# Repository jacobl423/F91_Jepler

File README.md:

# F91_Jepler

## Project Overview

The **F91_Jepler** is a complete redesign and evolution of the classic Casio F91W watch, inspired by the original [F91 Kepler](https://github.com/drpykachu/F91_Kepler) project. This project completely replaces the original internals of the watch, keeping only the original resin case and buttons, while adding an OLED display, a powerful Bluetooth-capable MCU, and a rechargeable battery system.

The redesign is in progress. Emulation, tooling and companion software are far along; the nRF52840 board itself is not fabricated, and fit and charging arrangements are not yet verified.

## Progress at a Glance

| Area | Status |
|---|---|
| **Hardware** | Original Kepler DipTrace PCBs converted to editable KiCad 10 projects; redesign draft board carried in the workbench app; BOMs and clock requirements documented. Nothing fabricated yet. |
| **Firmware** | Zephyr RTOS app boots under MCUboot in Renode: RTC-backed ticking clock, SSD1306 framebuffer over I2C, and the custom Notification and Clock GATT services ported to the Zephyr BLE stack. |
| **Emulation** | One-command firmware build with SHA-256 manifest, signed-image boot verification, browser watch viewer with real emulated framebuffer and GPIO buttons, headless boot check. |
| **Jepler Dev (macOS)** | Full Swift workbench: Renode session harness, UART terminal, watch face, firmware build/verify, automated test runner, UART test-bridge injectors, and a live KiCad suite (auto-reload viewer, 3D raytrace, DRC, Gerber export, diff). |
| **Companion app** | React + Capacitor mobile app (Android/iOS) with BLE scan/connect, GATT clock sync, mock driver and LCD watch face; **327/327 tests passing** (`npm test` in `Software/companion_app`). |

## Hardware Upgrades & Architecture

The original Kepler boards were authored in DipTrace; those files are retained unchanged in [`Hardware/PCB/`](Hardware/PCB) and have been converted into editable KiCad projects in [`Hardware/KiCad/`](Hardware/KiCad) (main board, display connector, debugger connector).

The nRF52840 redesign draft (A0) previously lived under `Hardware/KiCad/drafts/f91_jepler/`; that standalone copy was removed when the original boards were converted, and the same draft PCB now ships inside the workbench app at [`Software/macOS_App/F91JeplerEmulator/Resources/Embedded/f91_jepler.kicad_pcb`](Software/macOS_App/F91JeplerEmulator/Resources/Embedded/f91_jepler.kicad_pcb), where the Jepler Dev PCB tools open it by default. It remains an **unrouted electrical-core and placement draft, not a fabrication release**.

- **MCU:** Nordic nRF52840-QIAA, 7 × 7 mm AQFN73, with 1 MB flash and 256 KB RAM.
- **Display:** BuyDisplay ER-OLED0.83-1, a 0.83″ 96 × 39 monochrome OLED driven over I2C (SSD1306-class, Zephyr CFB framebuffer). Connector and supply details remain provisional.
- **Battery:** A small protected single-cell LiPo secured to the assembly replaces the earlier rechargeable coin-cell plan. Exact cell and fit remain provisional.
- **Power:** The draft includes a 3.0 V regulator (not a charger). Onboard charging, charge/load management and the charging connector still need design work.
- **Timekeeping:** External 32.768 kHz crystal feeding the nRF52840 RTC; see [clock circuit requirements](Hardware/CLOCKING.md).
- **Sensors:** An accelerometer and external flash remain optional; neither is in the draft.

### Bracket and charging contacts

Retain the original bracket as the mechanical reference. Its continuity, spring geometry, insulation and clearance around a new battery have not been measured. The user does not currently have it available, so those aspects remain provisional. The draft does not connect the bracket to a battery or charging net. Earlier split-cage and button-charging ideas in the historical project context are not approved electrical designs.

## Software Architecture

Moving to the nRF52840 means the original Texas Instruments SimpleLink firmware is being completely replaced. The new firmware is built on:
- **Zephyr RTOS / nRF Connect SDK:** The modern standard for Nordic BLE development.
- **MCUboot + SMP Server:** MCUboot is the first-stage bootloader with RSA-2048 signed images, and the SMP server allows safe, dual-bank Over-The-Air (OTA) Device Firmware Updates (DFU) directly from a smartphone, so the watch never needs to be opened for programming once flashed.

See [`Firmware/README.md`](Firmware/README.md) for build commands, the GATT service/characteristic map, and flashing notes.

## Development Tooling

### Jepler Dev — macOS workbench (`Software/macOS_App`)

A Swift app that combines the emulator, firmware pipeline and PCB tooling in one window:

- **Renode session harness:** launches Renode with the signed app image and matching MCUboot ELF, streams the UART console, and renders the live emulated framebuffer in a watch frame (the screen is driven by an in-repo `F91SSD1306.cs` model, not a mock drawing).
- **Firmware build & verify:** builds the Zephyr app plus its matching MCUboot image, signs it, and verifies full-file SHA-256 hashes against the generated `firmware-manifest.json` before loading anything into a session.
- **Automated tests & injectors:** boot-test runner and button-sequence presets that assert on firmware-reported state over the emulator-only UART test bridge, plus Notification/Clock service test panels (service-handler payloads, not real BLE/ATT traffic).
- **KiCad suite:** live auto-reload PCB viewer, 3D raytrace render, DRC via `kicad-cli` with SHA-256-pinned input snapshots and explicit pass / fail / inconclusive confidence, Gerber export, PCB diff and comparison, component inspector, board validation and GPIO pin audit against the compiled devicetree.

Build and launch from the repo root:

```bash
./run_emulator.sh          # builds "Jepler Dev.app" if missing, then opens it
```

### Emulation without the app (`Firmware/renode`)

```bash
bash Firmware/renode/build-display.sh   # west build + sign app & MCUboot, export manifest
bash Firmware/renode/watch-ui.sh        # watch viewer at http://127.0.0.1:8085
bash Firmware/renode/boot-check.sh      # headless MCUboot + app boot verification
```

See [`Firmware/renode/README.md`](Firmware/renode/README.md) for details, key bindings, and known limitations.

### Companion app (`Software/companion_app`)

React + Capacitor app for Android/iOS: scans for the watch by name or Clock Service UUID, connects over BLE, and syncs time / timezone / time mode / DST through the GATT clock characteristics, with a simulated-watch driver and an F-91W-style LCD for development. The suite covers serialization boundaries, the connection state machine, sync fault injection and a 4-tier E2E integration suite.

```bash
cd Software/companion_app
npm test          # Vitest: 327/327 passing
npm run typecheck && npm run build
```

## Current Project Status

- **Mechanicals:** Provisional outline and battery envelope; bracket fit unverified.
- **Schematic & PCB:** Original DipTrace boards converted to editable KiCad projects under [`Hardware/KiCad`](Hardware/KiCad); the nRF52840 redesign remains an unrouted draft (bundled with the macOS app). Original DipTrace files retained.
- **Firmware:** Zephyr, MCUboot and the ported GATT services run in Renode; see [emulation instructions](Firmware/renode/README.md). Signed-image boot and a flipped-byte rejection check pass; OTA swapping/rollback has not been tested. Simulation does not validate the physical board.
- **Software:** Jepler Dev workbench builds and launches via `run_emulator.sh`; companion app tests, typecheck and production build pass.

## Collaboration and Setup
Welcome collaborators! To get started with the repository, follow these steps:

1. **Clone the repository**:
   ```bash
   git clone <repository_url>
   cd f91_jepler
   ```

2. **Set up the Python Environment**:
   This project includes some utility scripts for parsing BOMs and STL files, and the Zephyr/west build uses the same environment. It is recommended to use a virtual environment:
   ```bash
   python3 -m venv .venv
   source .venv/bin/activate
   pip install -r requirements.txt
   ```

3. **Project Structure**:
   - `Firmware/`: Zephyr firmware source and Renode emulation tooling.
   - `Hardware/`: PCB designs (DipTrace originals and KiCad conversions), schematics, and BOMs.
   - `Software/`: Companion mobile app (`companion_app`), the Jepler Dev macOS workbench (`macOS_App`), and the legacy Android shell (`app`).

4. **Contributing**:
   - Please create a new branch for any feature or bugfix (e.g., `feature/add-new-sensor` or `bugfix/fix-display-glitch`).
   - Open a pull request against the `main` branch when your changes are ready for review.

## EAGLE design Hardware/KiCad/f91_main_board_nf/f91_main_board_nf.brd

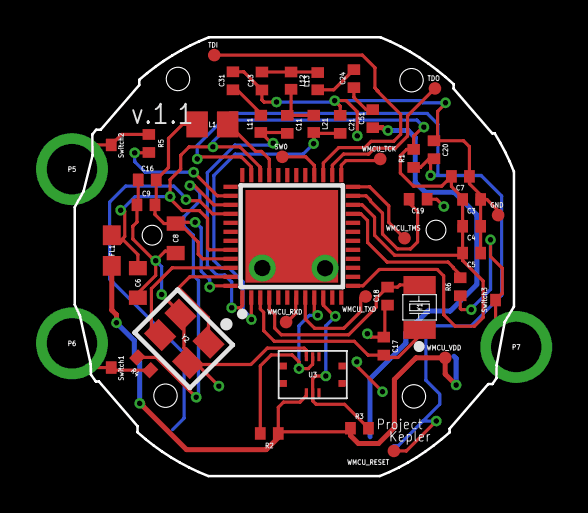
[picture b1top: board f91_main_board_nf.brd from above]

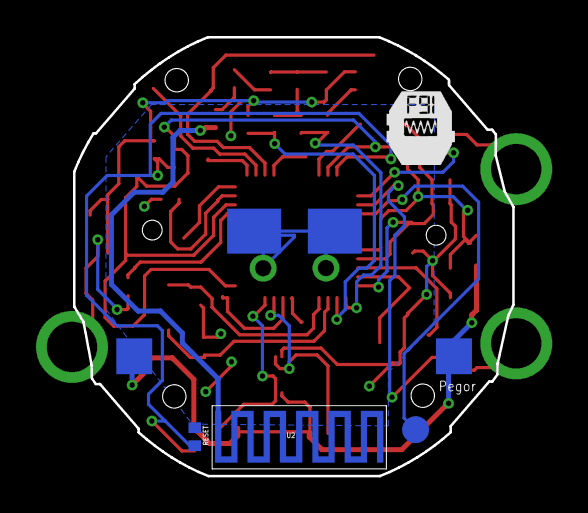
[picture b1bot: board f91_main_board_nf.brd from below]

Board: 2 copper layers, 24.4 x 24.4 mm, 59 parts (7 on the bottom side), 35 nets.

Parts:
: CC2640(long pads); RGZ0048A-VQFN-48(longer_pads)
C3, C4, C5, C7, C9, C16, C20: 100nF; CAP_0402
C6, C8: 10uF; CAP_0603
C11, C13, C21: 1pF; CAP_0402
C17, C18, C24: 12pF; CAP_0402
C19: 1uF; CAP_0402
C31: 6.8pF; CAP_0402
C51: 1.8pF; CAP_0402
FL1: BLM18HE152SN1; CAP_0603_FL1
GND: GND; single_probe_point
L1: 10uH; IND_0805
L11, L21: 2.4nH; IND_0402
L12, L13: 2nH; IND_0402
P5, P6, P7: CONN_01X01; PAD1
Pad1, Pad2: Pad
Pad3, Pad4: Pad; Pad_Pad3
Pad5: Pad; Pad_Pad5
Pad6, Pad7: Pad; Pad_Pad6
R1: 100k; RES_0402
R2, R3: 3.3k; RES_0402
R4, R5, R6: 100; RES_0402
RESET: N/A DO NOT CONNECT; RES_0402_RESET
SW0: SW0; single_probe_point
Switch1, Switch2: SingleConnect
Switch3: SingleConnect; SingleConnect_Switch3
TDI: TDI; single_probe_point
TDO: TDO; single_probe_point
U2: BT_Antenna; BT_ANTENNA
U3: 5050660622
WMCU_RESET: WMCU_RESET; single_probe_point_WMCU_RESET
WMCU_RXD: WMCU_RXD; single_probe_point
WMCU_TCK: single_probe point; single_probe_point
WMCU_TMS: WMCU_TMS; single_probe_point
WMCU_TXD: WMCU_TXD; single_probe_point_WMCU_TXD
WMCU_VDD: WMCU_VDD; single_probe_point
Y1: 32.768kHz; FC-135
Y2: 24MHz; TSX-3225

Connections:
Net_0: .49, C3.1, C4.1, C5.1, C6.1, C7.1, C8.1, C9.1, C13.1, C16.1, C17.1, C18.1, C19.1, C20.1, C21.1, C31.2, GND.1, Pad3.1, Pad4.1, Pad6.1, Pad7.1, RESET.1, U3.1, Y2.2, Y2.4
Net_1: FL1.1, Pad1.1, Pad2.1, R2.1, R3.1, U3.4, WMCU_VDD.1
Net_2: .13, .22, .34, .44, C3.2, C4.2, C5.2, C6.2, C7.2, FL1.2, R1.2
Net_3: .33, L1.1
Net_4: .45, .48, C8.2, C9.2, C16.2, L1.2
Net_5: .25, WMCU_TCK.1
Net_6: .24, WMCU_TMS.1
Net_7: .35, C20.2, R1.1, RESET.2, WMCU_RESET.1
Net_8: .3, C17.2, Y1.1
Net_9: .4, C18.2, Y1.2
Net_10: .23, C19.2
Net_11: .47, Y2.1
Net_12: .46, Y2.3
Net_13: .2, C21.2, L21.2
Net_14: .1, C11.2, L11.1
Net_15: C31.1, L11.2
Net_16: C11.1, L12.2, L21.1
Net_17: C13.2, L12.1, L13.2
Net_18: C24.2, L13.1
Net_19: C24.1, C51.2
Net_20: C51.1, U2.1, U2.1_1, U2.1_2, U2.1_3, U2.1_4, U2.1_5, U2.1_6, U2.1_7, U2.1_8, U2.1_9, U2.1_10, U2.1_11, U2.1_12, U2.1_13, U2.1_14, U2.1_15, U2.1_16, U2.1_17, U2.1_18, U2.1_19, U2.1_20
Net_21: .7, WMCU_RXD.1
Net_22: .8, WMCU_TXD.1
Net_23: .26, TDO.1
Net_24: .27, TDI.1
Net_25: .28, SW0.1
Net_26: .40, Pad5.1
Net_30: .10, R3.2, U3.5
Net_31: .9, R2.2, U3.2
Net_32: .21, R6.2
Net_33: .38, R5.2
Net_34: .39, R4.2
Net_35: P6.1, R4.1, Switch1.1
Net_36: P5.1, R5.1, Switch2.1
Net_37: P7.1, R6.1, Switch3.1
